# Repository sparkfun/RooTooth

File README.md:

RooTooth
========

[  
*RooTooth (DEV-12581)*](https://www.sparkfun.com/products/12581)

This is a cable-less solution developed for controlling your Roomba. The RooTooth v2 communicates with any Bluetooth&copy; enabled device using the Serial Port Profile (SPP). 

Repository Contents
-------------------
* **/Hardware** - All Eagle design files (.brd, .sch)
* **/Production** - Test bed files and production panel files

Version History
---------------
* [v16](https://www.sparkfun.com/products/10980) This version has older firmware and a pcb footprint with antenna pads.

License Information
-------------------
The hardware is released under [Creative Commons Share-alike 3.0](http://creativecommons.org/licenses/by-sa/3.0/).

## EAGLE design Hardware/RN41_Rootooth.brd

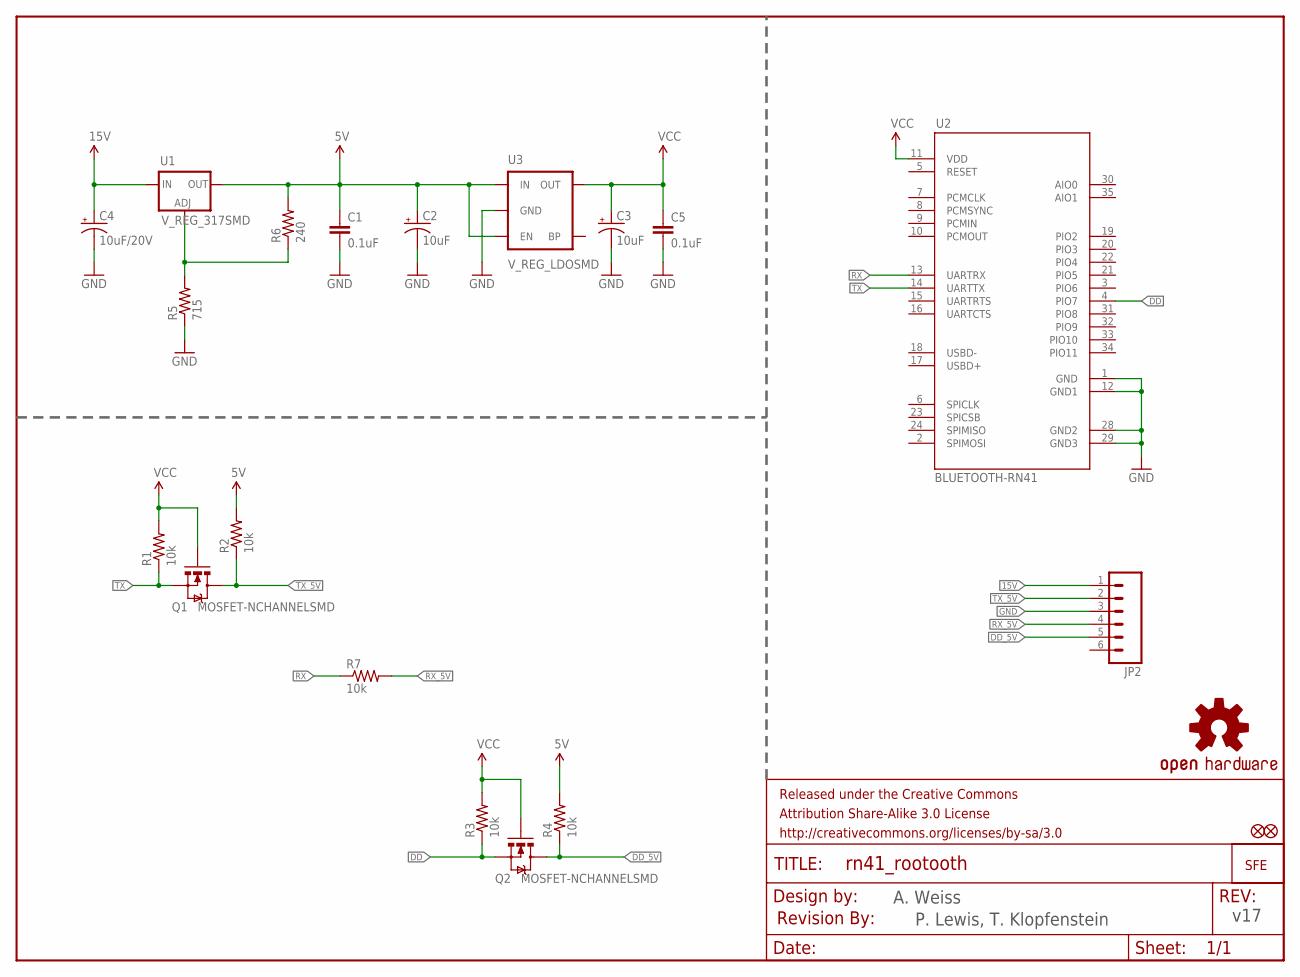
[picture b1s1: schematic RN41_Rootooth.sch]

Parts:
C1, C5: 0.1uF; 0603-CAP
C2, C3: 10uF; EIA3216
C4: 10uF/20V; EIA3528
FRAME1: FRAME-LETTER; CREATIVE_COMMONS
JP1, JP3: FIDUCIALUFIDUCIAL; MICRO-FIDUCIAL
JP2: M06SMD; 1X06-SMD
LOGO1: OSHW-LOGOS; OSHW-LOGO-S
Q1, Q2: MOSFET-NCHANNELSMD; SOT23-3
R1, R2, R3, R4, R7: 10k; 0603-RES
R5: 715; 0603-RES
R6: 240; 0603-RES
U1: V_REG_317SMD; SOT223
U2: BLUETOOTH-RN41; RN41
U3: V_REG_LDOSMD; SOT23-5
U$1: LOGO-SFENEW; SFE-NEW-WEBLOGO
U$2: REVISION

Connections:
5V: C1.1, C2.A (+), R2.2, R4.2, R6.2, U1.2 (OUT), U3.1 (IN), U3.3 (EN)
15V: C4.A (+), JP2.1, U1.3 (IN)
DD: Q2.2 (S), R3.1, U2.4 (PIO7)
DD_5V: JP2.5, Q2.3 (D), R4.1
GND: C1.2, C2.C (-), C3.C (-), C4.C (-), C5.2, JP2.3, R5.1, U2.1 (GND), U2.12 (GND1), U2.28 (GND2), U2.29 (GND3), U3.2 (GND)
unnamed: R5.2, R6.1, U1.1 (ADJ)
RX: R7.1, U2.13 (UARTRX)
RX_5V: JP2.4, R7.2
TX: Q1.2 (S), R1.1, U2.14 (UARTTX)
TX_5V: JP2.2, Q1.3 (D), R2.1
VCC: C3.A (+), C5.1, Q1.1 (G), Q2.1 (G), R1.2, R3.2, U2.11 (VDD), U3.5 (OUT)

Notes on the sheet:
v17
A. Weiss
P. Lewis, T. Klopfenstein

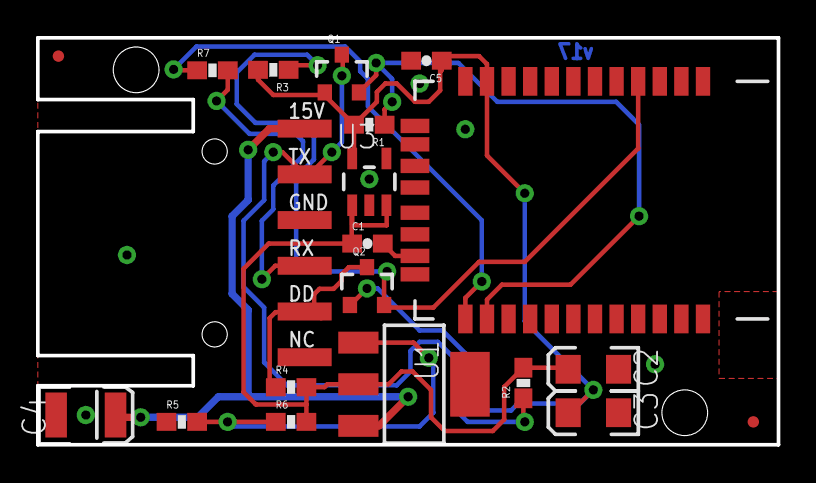
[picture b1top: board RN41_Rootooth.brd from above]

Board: 2 copper layers, 41.1 x 22.6 mm, 24 parts (2 on the bottom side), 11 nets.

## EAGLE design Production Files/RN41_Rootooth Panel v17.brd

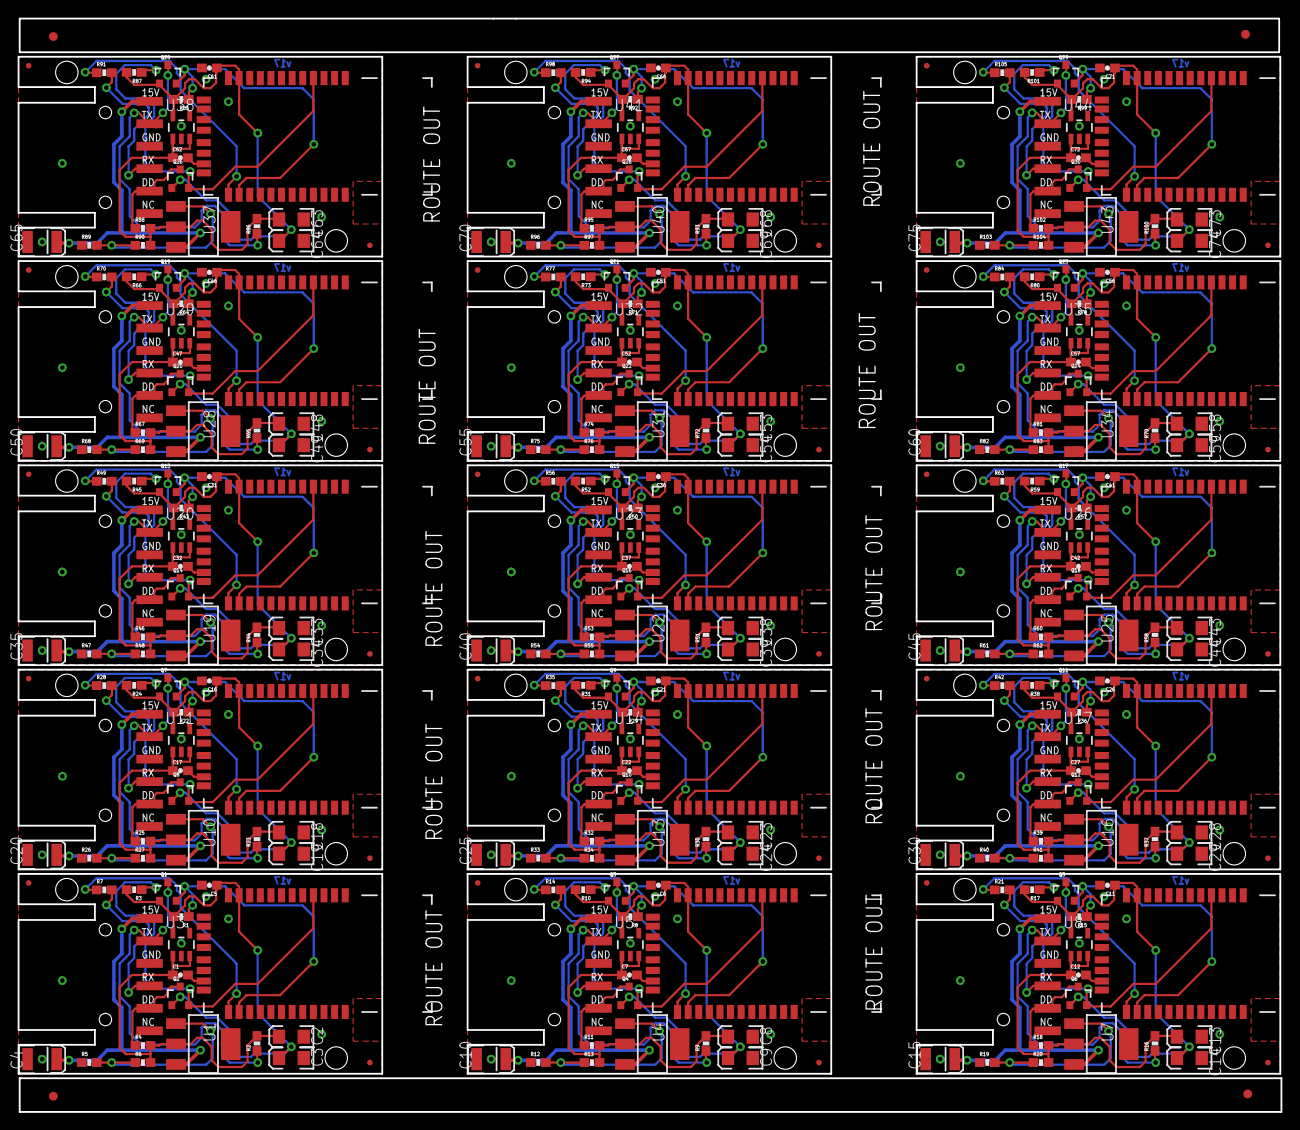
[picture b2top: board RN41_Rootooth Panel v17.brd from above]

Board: 2 copper layers, 142.9 x 123.7 mm, 334 parts (30 on the bottom side), 165 nets.

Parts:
C1, C5, C6, C7, C11, C12, C16, C17, C21, C22, C26, C27, C31, C32, C36, C37, C41, C42, C46, C47, C51, C52, C56, C57, C61, C62, C66, C67, C71, C72: 0.1uF; 0603-CAP
C2, C3, C8, C9, C13, C14, C18, C19, C23, C24, C28, C29, C33, C34, C38, C39, C43, C44, C48, C49, C53, C54, C58, C59, C63, C64, C68, C69, C73, C74: 10uF; EIA3216
C4, C10, C15, C20, C25, C30, C35, C40, C45, C50, C55, C60, C65, C70, C75: 10uF/20V; EIA3528
E$1, E$2, E$3, E$4: FIDUCIAL-1X2
JP1, JP3, JP5, JP6, JP8, JP9, JP11, JP12, JP14, JP15, JP17, JP18, JP20, JP21, JP23, JP24, JP26, JP27, JP29, JP30, JP32, JP33, JP35, JP36, JP38, JP39, JP41, JP42, JP44, JP45: FIDUCIALUFIDUCIAL; MICRO-FIDUCIAL
JP2, JP4, JP7, JP10, JP13, JP16, JP19, JP22, JP25, JP28, JP31, JP34, JP37, JP40, JP43: 1X06-SMD
LOGO1, LOGO2, LOGO3, LOGO4, LOGO5, LOGO6, LOGO7, LOGO8, LOGO9, LOGO10, LOGO11, LOGO12, LOGO13, LOGO14, LOGO15: OSHW-LOGOS; OSHW-LOGO-S
Q1, Q2, Q3, Q4, Q5, Q6, Q7, Q8, Q9, Q10, Q11, Q12, Q13, Q14, Q15, Q16, Q17, Q18, Q19, Q20, Q21, Q22, Q23, Q24, Q25, Q26, Q27, Q28, Q29, Q30: MOSFET-NCHANNELSMD; SOT23-3
R1, R2, R3, R4, R7, R8, R9, R10, R11, R14, R15, R16, R17, R18, R21, R22, R23, R24, R25, R28, R29, R30, R31, R32, R35, R36, R37, R38, R39, R42, R43, R44, R45, R46, R49, R50, R51, R52, R53, R56, R57, R58, R59, R60, R63, R64, R65, R66, R67, R70, R71, R72, R73, R74, R77, R78, R79, R80, R81, R84, R85, R86, R87, R88, R91, R92, R93, R94, R95, R98, R99, R100, R101, R102, R105: 10k; 0603-RES
R5, R12, R19, R26, R33, R40, R47, R54, R61, R68, R75, R82, R89, R96, R103: 715; 0603-RES
R6, R13, R20, R27, R34, R41, R48, R55, R62, R69, R76, R83, R90, R97, R104: 240; 0603-RES
U1, U4, U7, U10, U13, U16, U19, U22, U25, U28, U31, U34, U37, U40, U43: V_REG_317SMD; SOT223
U2, U6, U9, U12, U15, U18, U21, U24, U27, U30, U33, U36, U39, U42, U45: BLUETOOTH-RN41; RN41
U3, U5, U8, U11, U14, U17, U20, U23, U26, U29, U32, U35, U38, U41, U44: V_REG_LDOSMD; SOT23-5
U$1, U$2, U$3, U$4, U$5, U$6, U$7, U$8, U$9, U$10, U$11, U$12, U$13, U$14, U$15: LOGO-SFENEW; SFE-NEW-WEBLOGO

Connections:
5V: C1.1, C2.A, R2.2, R4.2, R6.2, U1.2, U3.1, U3.3
5V1: C7.1, C8.A, R9.2, R11.2, R13.2, U4.2, U5.1, U5.3
5V2: C12.1, C13.A, R16.2, R18.2, R20.2, U7.2, U8.1, U8.3
5V3: C17.1, C18.A, R23.2, R25.2, R27.2, U10.2, U11.1, U11.3
5V4: C22.1, C23.A, R30.2, R32.2, R34.2, U13.2, U14.1, U14.3
5V5: C27.1, C28.A, R37.2, R39.2, R41.2, U16.2, U17.1, U17.3
5V6: C32.1, C33.A, R44.2, R46.2, R48.2, U19.2, U20.1, U20.3
5V7: C37.1, C38.A, R51.2, R53.2, R55.2, U22.2, U23.1, U23.3
5V8: C42.1, C43.A, R58.2, R60.2, R62.2, U25.2, U26.1, U26.3
5V9: C47.1, C48.A, R65.2, R67.2, R69.2, U28.2, U29.1, U29.3
5V10: C52.1, C53.A, R72.2, R74.2, R76.2, U31.2, U32.1, U32.3
5V11: C57.1, C58.A, R79.2, R81.2, R83.2, U34.2, U35.1, U35.3
5V12: C62.1, C63.A, R86.2, R88.2, R90.2, U37.2, U38.1, U38.3
5V13: C67.1, C68.A, R93.2, R95.2, R97.2, U40.2, U41.1, U41.3
5V14: C72.1, C73.A, R100.2, R102.2, R104.2, U43.2, U44.1, U44.3
15V: C4.A, JP2.1, U1.3
15V1: C10.A, JP4.1, U4.3
15V2: C15.A, JP7.1, U7.3
15V3: C20.A, JP10.1, U10.3
15V4: C25.A, JP13.1, U13.3
15V5: C30.A, JP16.1, U16.3
15V6: C35.A, JP19.1, U19.3
15V7: C40.A, JP22.1, U22.3
15V8: C45.A, JP25.1, U25.3
15V9: C50.A, JP28.1, U28.3
15V10: C55.A, JP31.1, U31.3
15V11: C60.A, JP34.1, U34.3
15V12: C65.A, JP37.1, U37.3
15V13: C70.A, JP40.1, U40.3
15V14: C75.A, JP43.1, U43.3
DD: Q2.2, R3.1, U2.4
DD1: Q4.2, R10.1, U6.4
DD2: Q6.2, R17.1, U9.4
DD3: Q8.2, R24.1, U12.4
DD4: Q10.2, R31.1, U15.4
DD5: Q12.2, R38.1, U18.4
DD6: Q14.2, R45.1, U21.4
DD7: Q16.2, R52.1, U24.4
DD8: Q18.2, R59.1, U27.4
DD9: Q20.2, R66.1, U30.4
DD10: Q22.2, R73.1, U33.4
DD11: Q24.2, R80.1, U36.4
DD12: Q26.2, R87.1, U39.4
DD13: Q28.2, R94.1, U42.4
DD14: Q30.2, R101.1, U45.4
DD_5V: JP2.5, Q2.3, R4.1
DD_5V1: JP4.5, Q4.3, R11.1
DD_5V2: JP7.5, Q6.3, R18.1
DD_5V3: JP10.5, Q8.3, R25.1
DD_5V4: JP13.5, Q10.3, R32.1
DD_5V5: JP16.5, Q12.3, R39.1
DD_5V6: JP19.5, Q14.3, R46.1
DD_5V7: JP22.5, Q16.3, R53.1
DD_5V8: JP25.5, Q18.3, R60.1
DD_5V9: JP28.5, Q20.3, R67.1
DD_5V10: JP31.5, Q22.3, R74.1
DD_5V11: JP34.5, Q24.3, R81.1
DD_5V12: JP37.5, Q26.3, R88.1
DD_5V13: JP40.5, Q28.3, R95.1
DD_5V14: JP43.5, Q30.3, R102.1
GND: C1.2, C2.C, C3.C, C4.C, C5.2, JP2.3, R5.1, U2.1, U2.12, U2.28, U2.29, U3.2
GND1: C6.2, C7.2, C8.C, C9.C, C10.C, JP4.3, R12.1, U5.2, U6.1, U6.12, U6.28, U6.29
GND2: C11.2, C12.2, C13.C, C14.C, C15.C, JP7.3, R19.1, U8.2, U9.1, U9.12, U9.28, U9.29
GND3: C16.2, C17.2, C18.C, C19.C, C20.C, JP10.3, R26.1, U11.2, U12.1, U12.12, U12.28, U12.29
GND4: C21.2, C22.2, C23.C, C24.C, C25.C, JP13.3, R33.1, U14.2, U15.1, U15.12, U15.28, U15.29
GND5: C26.2, C27.2, C28.C, C29.C, C30.C, JP16.3, R40.1, U17.2, U18.1, U18.12, U18.28, U18.29
GND6: C31.2, C32.2, C33.C, C34.C, C35.C, JP19.3, R47.1, U20.2, U21.1, U21.12, U21.28, U21.29
GND7: C36.2, C37.2, C38.C, C39.C, C40.C, JP22.3, R54.1, U23.2, U24.1, U24.12, U24.28, U24.29
GND8: C41.2, C42.2, C43.C, C44.C, C45.C, JP25.3, R61.1, U26.2, U27.1, U27.12, U27.28, U27.29
GND9: C46.2, C47.2, C48.C, C49.C, C50.C, JP28.3, R68.1, U29.2, U30.1, U30.12, U30.28, U30.29
GND10: C51.2, C52.2, C53.C, C54.C, C55.C, JP31.3, R75.1, U32.2, U33.1, U33.12, U33.28, U33.29
GND11: C56.2, C57.2, C58.C, C59.C, C60.C, JP34.3, R82.1, U35.2, U36.1, U36.12, U36.28, U36.29
GND12: C61.2, C62.2, C63.C, C64.C, C65.C, JP37.3, R89.1, U38.2, U39.1, U39.12, U39.28, U39.29
GND13: C66.2, C67.2, C68.C, C69.C, C70.C, JP40.3, R96.1, U41.2, U42.1, U42.12, U42.28, U42.29
GND14: C71.2, C72.2, C73.C, C74.C, C75.C, JP43.3, R103.1, U44.2, U45.1, U45.12, U45.28, U45.29
unnamed: R12.2, R13.1, U4.1
unnamed: R5.2, R6.1, U1.1
unnamed: R19.2, R20.1, U7.1
unnamed: R26.2, R27.1, U10.1
unnamed: R33.2, R34.1, U13.1
unnamed: R40.2, R41.1, U16.1
unnamed: R47.2, R48.1, U19.1
unnamed: R54.2, R55.1, U22.1
unnamed: R61.2, R62.1, U25.1
unnamed: R68.2, R69.1, U28.1
unnamed: R75.2, R76.1, U31.1
unnamed: R82.2, R83.1, U34.1
unnamed: R89.2, R90.1, U37.1
unnamed: R96.2, R97.1, U40.1
unnamed: R103.2, R104.1, U43.1
RX: R7.1, U2.13
RX1: R14.1, U6.13
RX2: R21.1, U9.13
RX3: R28.1, U12.13
RX4: R35.1, U15.13
RX5: R42.1, U18.13
RX6: R49.1, U21.13
RX7: R56.1, U24.13
RX8: R63.1, U27.13
RX9: R70.1, U30.13
RX10: R77.1, U33.13
RX11: R84.1, U36.13
RX12: R91.1, U39.13
RX13: R98.1, U42.13
RX14: R105.1, U45.13
RX_5V: JP2.4, R7.2
RX_5V1: JP4.4, R14.2
RX_5V2: JP7.4, R21.2
RX_5V3: JP10.4, R28.2
RX_5V4: JP13.4, R35.2
RX_5V5: JP16.4, R42.2
RX_5V6: JP19.4, R49.2
RX_5V7: JP22.4, R56.2
RX_5V8: JP25.4, R63.2
RX_5V9: JP28.4, R70.2
RX_5V10: JP31.4, R77.2
RX_5V11: JP34.4, R84.2
RX_5V12: JP37.4, R91.2
RX_5V13: JP40.4, R98.2
RX_5V14: JP43.4, R105.2
TX: Q1.2, R1.1, U2.14
TX1: Q3.2, R8.1, U6.14
TX2: Q5.2, R15.1, U9.14
TX3: Q7.2, R22.1, U12.14
TX4: Q9.2, R29.1, U15.14
TX5: Q11.2, R36.1, U18.14
TX6: Q13.2, R43.1, U21.14
TX7: Q15.2, R50.1, U24.14
TX8: Q17.2, R57.1, U27.14
TX9: Q19.2, R64.1, U30.14
TX10: Q21.2, R71.1, U33.14
TX11: Q23.2, R78.1, U36.14
TX12: Q25.2, R85.1, U39.14
TX13: Q27.2, R92.1, U42.14
TX14: Q29.2, R99.1, U45.14
TX_5V: JP2.2, Q1.3, R2.1
TX_5V1: JP4.2, Q3.3, R9.1
TX_5V2: JP7.2, Q5.3, R16.1
TX_5V3: JP10.2, Q7.3, R23.1
TX_5V4: JP13.2, Q9.3, R30.1
TX_5V5: JP16.2, Q11.3, R37.1
TX_5V6: JP19.2, Q13.3, R44.1
TX_5V7: JP22.2, Q15.3, R51.1
TX_5V8: JP25.2, Q17.3, R58.1
TX_5V9: JP28.2, Q19.3, R65.1
TX_5V10: JP31.2, Q21.3, R72.1
TX_5V11: JP34.2, Q23.3, R79.1
TX_5V12: JP37.2, Q25.3, R86.1
TX_5V13: JP40.2, Q27.3, R93.1
TX_5V14: JP43.2, Q29.3, R100.1
VCC: C3.A, C5.1, Q1.1, Q2.1, R1.2, R3.2, U2.11, U3.5
VCC1: C6.1, C9.A, Q3.1, Q4.1, R8.2, R10.2, U5.5, U6.11
VCC2: C11.1, C14.A, Q5.1, Q6.1, R15.2, R17.2, U8.5, U9.11
VCC3: C16.1, C19.A, Q7.1, Q8.1, R22.2, R24.2, U11.5, U12.11
VCC4: C21.1, C24.A, Q9.1, Q10.1, R29.2, R31.2, U14.5, U15.11
VCC5: C26.1, C29.A, Q11.1, Q12.1, R36.2, R38.2, U17.5, U18.11
VCC6: C31.1, C34.A, Q13.1, Q14.1, R43.2, R45.2, U20.5, U21.11
VCC7: C36.1, C39.A, Q15.1, Q16.1, R50.2, R52.2, U23.5, U24.11
VCC8: C41.1, C44.A, Q17.1, Q18.1, R57.2, R59.2, U26.5, U27.11
VCC9: C46.1, C49.A, Q19.1, Q20.1, R64.2, R66.2, U29.5, U30.11
VCC10: C51.1, C54.A, Q21.1, Q22.1, R71.2, R73.2, U32.5, U33.11
VCC11: C56.1, C59.A, Q23.1, Q24.1, R78.2, R80.2, U35.5, U36.11
VCC12: C61.1, C64.A, Q25.1, Q26.1, R85.2, R87.2, U38.5, U39.11
VCC13: C66.1, C69.A, Q27.1, Q28.1, R92.2, R94.2, U41.5, U42.11
VCC14: C71.1, C74.A, Q29.1, Q30.1, R99.2, R101.2, U44.5, U45.11

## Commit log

2013-06-05 Adding GITIGNORE
2013-07-11 Updated board files for v17
2013-07-15 Updated Revision to symbol layer
2013-07-17 v17 production readied
    created panel of 15
2013-12-11 Adding new version info to README
2025-06-27 Update README.md
    Updating link

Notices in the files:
parts and their libraries:
SparkFun-Aesthetics: Licensing: CC v3.0 Share-Alike You are welcome to use this library for commercial purposes.
SparkFun-Aesthetics: Released under the Creative Commons Attribution Share-Alike 3.0 License
SparkFun-Aesthetics: Released under the Creative Commons
